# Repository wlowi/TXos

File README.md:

# TXos

Diese Software ist ein Beispiel für eine RC Sender firmware.<br/>
Es wird keine Haftung für Schäden jeglicher Art übernommen.

Bitte beachten Sie die Lizenz.

---

This is an example of a RC transmitter software.<br/>
In no event shall the authors or copyright holders be liable for any claim, damage or other liability.

Please obey the license.

---

[Bedienungsanleitung](MANUAL.md)

[Robbe Supra PCMS Umbau](SUPRA.md)

<span style="color:red">Achtung: Crossfire Protokoll ist neu und noch nicht vollständig getestet.</span>

[Crossfire / ELRS Howto](ELRS.md)

---

## Unterstützte Hardware

### Arduino CPU Board

- Joy-IT ADR MEGA2560PRO
- ESP32 DevKit (EXPERIMENTELL UND UNGETESTED, NICHT BENUTZEN!)

### Display

- ST7735 1,8" Color TFT Display

### Drück-Dreh Encoder

- Z.Bsp. von ALPS

### PPM HF-Module

- Z.Bsp. Spektrum Modul für Graupner MC-24 / MC-22 oder Jeti TU2 Modul.

### Seriell angesteuerte HF-Module

<span style="color:red">Achtung: EXPERIMENTELL UND UNGETESTED, NICHT BENUTZEN!</span>

- Spektrum X1TXN
- ELRS Full Duplex (interne Module) Bzw. Empfänger mit RxAsTx Firmware.

---

## Features

- Bis zu 6 Analoge Eingänge
- Bis zu 4 Eingänge für analogen Trimm
- Trimmspeicher
- Bin zu 6 Schalteingänge für 2 oder 3 Stufenschalter
- 12 Interne Kanäle
    MOT, QR, QR2, HR, SR, WK, WK2, LK, LK2, Fwk, K8, K9
    MOT = Motor
    QR = Querruder
    HR = Höhenruder
    SR = Seitenruder
    WK = Wölbklappen
    LK = Landeklappen
    Fwk = Fahrwerk
    K8, K9 = freie Kanäle
- Bis zu 12 Servo Ausgänge
- PPM Erzeugung (22.5 mSec. Frames)
- Unterstützt serielles Spektrum HF Modul (X1TXN)
- Unterstützt CRSF (Crossfire) Protokoll zur Ansteuerung von ELRS HF Modulen
- Spannungsüberwachung
- Display 8 x 13 Zeichen
- Deutsche und Englische Benutzeroberfläche
- Bedienung über Drück-Dreh Encoder
- Piepser
- Relais zum Ausschalten der HF-Modul Stromversorgung
- Relais zum Bedienen eines Bind-Tasters
- Geber Umkehr und Limitter
- Delta Mischer und V-Leitwerks Mischer
- Fertige Mischer für
    QR => SR
    QR => WK
    LK => QR
    LK => WK
    LK => HR
    WK => QR
    WK => HR
    HR => QR
    HR => WK
    SR => HR
- 3 Freie Mischer
- Kanal Laufzeit Verzögerung bis 10 Sek. (Ende zu Ende)
- 3 Geberschalter
- 3 Schaltkanäle
- 14 Modellspeicher
- 3 Flugphasen (aus Normal, Thermik, Speed, Start, Landung, Akro, Akro2, Strecke, Schlepp)
- Phasentrim für QR,WK,LK,HR
- Dual Rate und Exponential Funktion über Phasen für QR, SR und HR
- 3 Logische Schalter. (Boolsche Verknüpfung von bis zu 3 Schaltern)
- Freie Zuordnung der Geber zu Kanälen
- Freie Zuordnung der Kanäle zu Servo Ausgängen
- Servo Mitte, Umkehr und Limitter
- Timer (Wahlweise Gasabhängig)
- Motor-Aus Schalter
- Bind Funktion (Falls Support vom HF-Modul besteht)
- Reichweiten Test Funktion (Falls Support vom HF-Modul besteht)
- Servo Monitor
- Schalter Monitor
- Import und Export der Modelle zum PC über USB Schnittstelle

---

## Blockschaltbild der Funktionen

---

## Change History

```
0.5.19 Some UI improvements.
       Keep value of logical "Mot" channel to correct value if engine cut is enabled. 
0.5.18 CRSF and Spektrum Telemetry. First cut. 
0.5.17 Disable sleep. Fix input names array.
0.5.16 CRSF Protokol
0.5.15 Serielles Spektrum Protokol
0.5.14 internes Release
0.5.13 Notorstart Modul
0.5.12 Veränderte schaltung der Flugphasen
0.5.11 Logische Schalter: invertierte Schalter.
0.5.10 Timer wahlweise Gasabhängig.
       Alle Schalter in SWx umbenannt.
0.5.9 Landeklappen Modul.
0.5.8 Watchdog fix beim schreiben ins EEPROM und serial I/O
0.5.7 Servo Verzögerung Modul.
0.5.6 Servo Weg Modul.
0.5.5 Experimental ESP 32 support.
0.5.4 External user terminal support.
0.5.3 Experimental external user terminal support.
0.5.2 Template based configuration
0.5.1 Modul import fixed. Geber Weg getrennt pos. und neg.
0.5.0 Modell import/export. Modell management.
```

---

## Installation

### Übersetzen mit der Arduino IDE

#### Für ADR MEGA2560PRO

Benötigte Arduino Libraries
- Adafruit ST7736 and ST7789 Library
- Adafruit GFX Library

```
cd TXos
./mklinks atmega2560
```

Dieses Kommando verlinkt die Dateien im `src` Verzeichnis nach `TXos`.

Fall noch keine lokale Konfigurationsdtei TXosLocalConfig.h existiert wird diese von einer Musterdatei kopiert und muss an die eigen Hardware konfiguration angepasst werden.

Mit der Arduino IDE kann dann in diesem Verzeichnis TXos compiliert werden.

Notwendige Einstellungen der Arduino IDE

TO_BE_COMPLETED

#### Für ESP32 (EXPERIMENTELL UND UNGETESTED, NICHT BENUTZEN!)

Benötigte Arduino Libraries
- TFT_eSPI

```
cd TXos
./mklinks esp32
```

Mit der Arduino IDE kann dann in diesem Verzeichnis TXos compiliert werden.

Notwendinge Einstellungen der Arduino IDE

---

### Grundsätzliche Konfiguration:

Wechsel zu Verzeichnis TXos/TXos

Unter Linux ./mklinks.sh \<Platform\><br/>
ausführen.

Unter Windows mkcopy.bat \<Platform\><br/>
ausführen.

Als Platform wird zur Zeit nur atmega2560 unterstützt.

Existiert noch keine Datei TXosLocalConfig.h wird diese aus TXosLocalConfig.template neu erzeugt.

Konfiguration in TXosLocalConfig.h anpassen.

Hier werden eingestellt:

- Die Sprache der Benutzeroberfläche
- Das verwendete HF Modul
- Die Anzahl der PPM Kanäle
- Die Anzahl der Analog Kanäle
- Die Anzahl der Schalter (mechanische, logische und Sonderschalter)
- Die Anzahl der Flugphasen
- Die Anzahl der freien Mischer

Beispiel:

```

$ ./mklinks.sh atmega2560
Configuring for atmega2560
Link from ../src
   ../src/Comm.cpp  =>  Comm.cpp
   ../src/ConfigBlock.cpp  =>  ConfigBlock.cpp
   ../src/HomeScreen.cpp  =>  HomeScreen.cpp
  .
  .
  .
   atmega2560/OutputImpl.h  =>  OutputImpl.h
   atmega2560/PortsImpl.h  =>  PortsImpl.h

Local config does not exist.
A new TXosLocalConfig.h has been generated by copying the template file.
Please modify your local config to your needs.

```

---

## TXos Simulator

Der Simulator verwendet die `wxWidgets` library. Zum installieren:

```
apt install gcc make libwxgtk3.0-gtk3-dev

cd src
make clean
make -j
./TXosTest
```

---

## Unit test

```
cd test
make clean
make -j unittest
./TXosUnitTest
```

Achtung: `make clean unittest` funktioniert nicht!

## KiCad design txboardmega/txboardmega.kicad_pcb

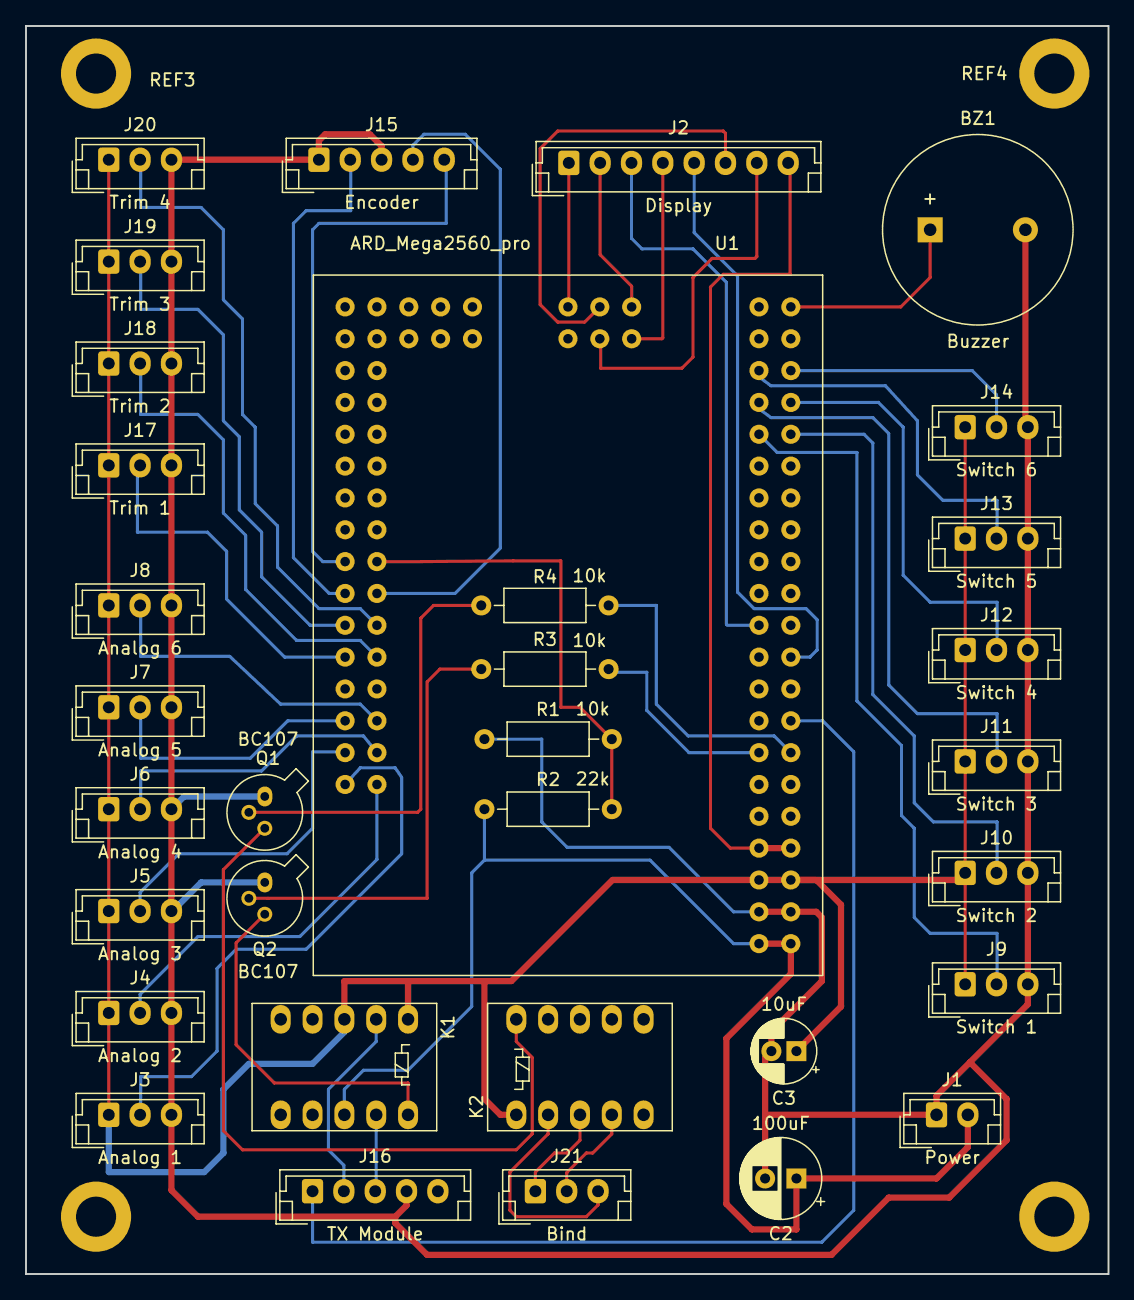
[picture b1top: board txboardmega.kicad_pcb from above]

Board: 2 copper layers, 86.4 x 99.6 mm, 37 parts (0 on the bottom side), 44 nets.

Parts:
BZ1: Buzzer; Buzzer_15x7.5RM7.6
C2: 100uF; CP_Radial_D6.3mm_P2.50mm
C3: 10uF; CP_Radial_D5.0mm_P2.00mm
J1: Power; JST_EH_B2B-EH-A_1x02_P2.50mm_Vertical
J2: Display; JST_EH_B8B-EH-A_1x08_P2.50mm_Vertical
J3: Analog 1; JST_EH_B3B-EH-A_1x03_P2.50mm_Vertical
J4: Analog 2; JST_EH_B3B-EH-A_1x03_P2.50mm_Vertical
J5: Analog 3; JST_EH_B3B-EH-A_1x03_P2.50mm_Vertical
J6: Analog 4; JST_EH_B3B-EH-A_1x03_P2.50mm_Vertical
J7: Analog 5; JST_EH_B3B-EH-A_1x03_P2.50mm_Vertical
J8: Analog 6; JST_EH_B3B-EH-A_1x03_P2.50mm_Vertical
J9: Switch 1; JST_EH_B3B-EH-A_1x03_P2.50mm_Vertical
J10: Switch 2; JST_EH_B3B-EH-A_1x03_P2.50mm_Vertical
J11: Switch 3; JST_EH_B3B-EH-A_1x03_P2.50mm_Vertical
J12: Switch 4; JST_EH_B3B-EH-A_1x03_P2.50mm_Vertical
J13: Switch 5; JST_EH_B3B-EH-A_1x03_P2.50mm_Vertical
J14: Switch 6; JST_EH_B3B-EH-A_1x03_P2.50mm_Vertical
J15: Encoder; JST_EH_B5B-EH-A_1x05_P2.50mm_Vertical
J16: TX Module; JST_EH_B5B-EH-A_1x05_P2.50mm_Vertical
J17: Trim 1; JST_EH_B3B-EH-A_1x03_P2.50mm_Vertical
J18: Trim 2; JST_EH_B3B-EH-A_1x03_P2.50mm_Vertical
J19: Trim 3; JST_EH_B3B-EH-A_1x03_P2.50mm_Vertical
J20: Trim 4; JST_EH_B3B-EH-A_1x03_P2.50mm_Vertical
J21: Bind; JST_EH_B3B-EH-A_1x03_P2.50mm_Vertical
K1: HF on; Relay_DPDT_FRT5
K2: Bind; Relay_DPDT_FRT5
Q1, Q2: BC107; TO-18-3
R1, R3, R4: 10k; R_Axial_DIN0207_L6.3mm_D2.5mm_P10.16mm_Horizontal
R2: 22k; R_Axial_DIN0207_L6.3mm_D2.5mm_P10.16mm_Horizontal
REF1, REF2, REF3, REF4: MountingHole_3.2mm_M3_DIN965_Pad
U1: ARD_Mega2560_pro

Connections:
unnamed: BZ1.1, U1.42
unnamed: BZ1.2, C2.2, C3.2, J1.1, J3.3, J4.3, J5.3, J6.3, J7.3, J8.3, J9.3, J10.3, J11.3, J12.3, J13.3, J14.3, J15.1, J15.3, J16.4, J17.3, J18.3, J19.3, J20.3, Q1.1, Q2.1, R1.1, U1.3, U1.4
unnamed: C2.1, J1.2, K1.8, R2.1, U1.1, U1.2
unnamed: C3.1, J3.1, J4.1, J5.1, J6.1, J7.1, J8.1, J9.1, J10.1, J11.1, J12.1, J13.1, J14.1, J17.1, J18.1, J19.1, J20.1, K1.1, K1.3, K2.1, U1.5, U1.6
unnamed: J2.1, U1.81
unnamed: J2.2, U1.85
unnamed: J2.3, U1.21
unnamed: J2.4, U1.86
unnamed: J2.5, U1.20
unnamed: J2.6, U1.83
unnamed: J2.7, U1.84
unnamed: J2.8, U1.7, U1.8
unnamed: J3.2, U1.43
unnamed: J4.2, U1.44
unnamed: J5.2, U1.45
unnamed: J6.2, U1.46
unnamed: J7.2, U1.47
unnamed: J8.2, U1.48
unnamed: J9.2, U1.33
unnamed: J10.2, U1.34
unnamed: J11.2, U1.35
unnamed: J12.2, U1.36
unnamed: J13.2, U1.37
unnamed: J14.2, U1.38
unnamed: J15.2, U1.55
unnamed: J15.4, U1.56
unnamed: J15.5, U1.57
unnamed: J16.1, U1.16
unnamed: J16.2, K1.2
unnamed: J16.3, K1.9
unnamed: J17.2, U1.51
unnamed: J18.2, U1.52
unnamed: J19.2, U1.53
unnamed: J20.2, U1.54
unnamed: J21.1, K2.3
unnamed: J21.2, K2.4
unnamed: J21.3, K2.2
unnamed: K1.10, Q2.3
unnamed: K2.10, Q1.3
unnamed: Q1.2, R4.2
unnamed: Q2.2, R3.1
unnamed: R1.2, R2.2, U1.58
unnamed: R3.2, U1.13
unnamed: R4.1, U1.14

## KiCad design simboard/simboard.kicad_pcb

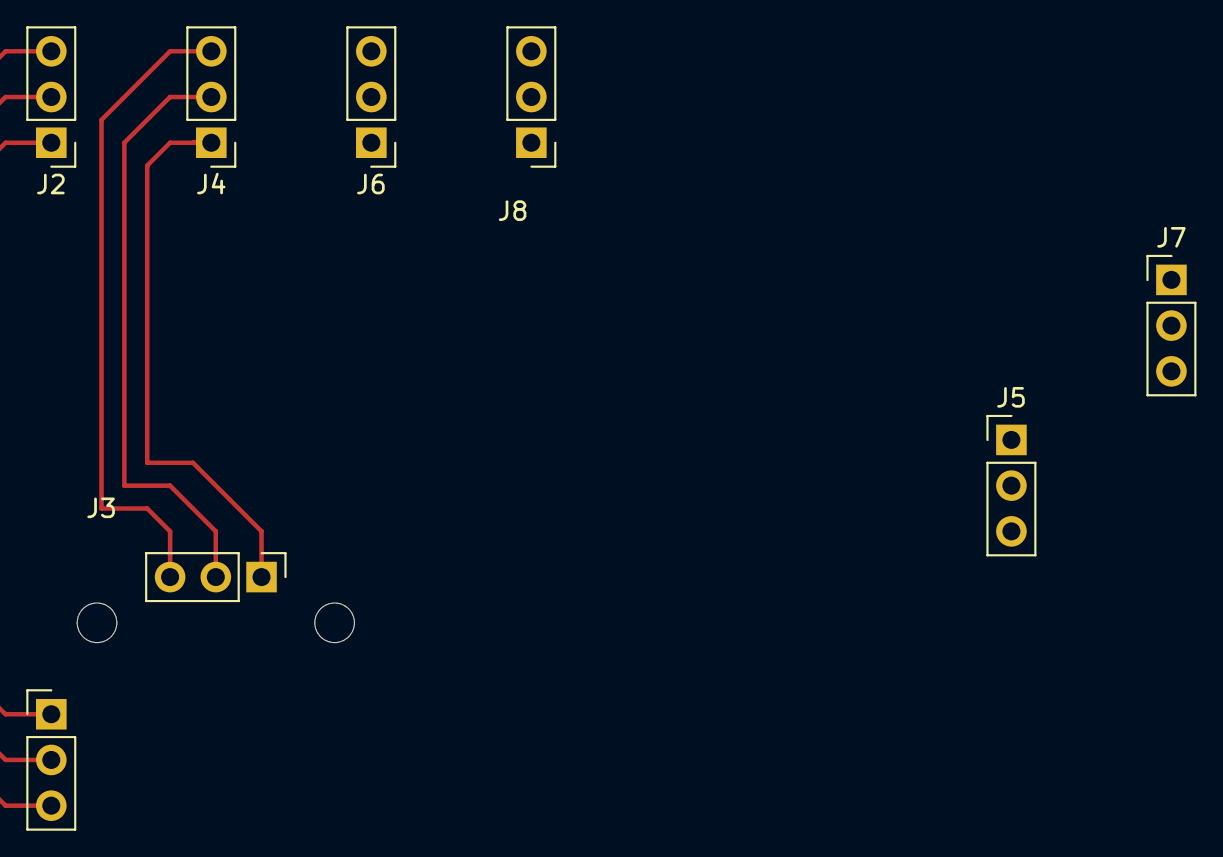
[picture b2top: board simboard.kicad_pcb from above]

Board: 2 copper layers, 8 parts (0 on the bottom side), 12 nets.

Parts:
J1, J2, J3, J4, J5, J6, J7, J8: Conn_01x03; PinHeader_1x03_P2.54mm_Vertical

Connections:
unnamed: J1.1, J2.1
unnamed: J1.2, J2.2
unnamed: J1.3, J2.3
unnamed: J3.1, J4.1
unnamed: J3.2, J4.2
unnamed: J3.3, J4.3
unnamed: J5.1, J6.1
unnamed: J5.2, J6.2
unnamed: J5.3, J6.3
unnamed: J7.1, J8.1
unnamed: J7.2, J8.2
unnamed: J7.3, J8.3

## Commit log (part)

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2022-04-13 Added src/default. Added gitignore
2022-04-30 Remote control simulation test framework.
2022-05-01 EEPROM emulation; ModuleManager; ServoReverse
2022-05-01 PPM improvements. KICAD Layout
2022-05-06 Intermediate checkin.
2022-05-18 SelectList added
2022-05-20 Table editable
2022-05-22 Some reorg
2022-05-23 Model edit module
2022-05-25 Fixed model select
2022-05-25 Fixed name editing
2022-05-25 Added EngineCut module
2022-05-31 Implementation or atmega2560
2022-05-31 Add Kicad design for mega 2560
2022-06-16 PPM generation implemented.
2022-06-19 PCB update
2022-06-30 txmegaboard updates and code cleanup
2022-06-30 Fixed LOG parameters
2022-07-03 Switch states and some cleanup
2022-08-21 Add ServoMonitor and SwitchMonitor
2022-08-27 Controls refactored
2022-09-10 Board for Robbe Supra
2022-09-25 Added Ports and Buzzer
2022-09-29 Complete Ports and Buzzer
2022-11-19 UI improvements. System setup (incomplete).
2022-11-24 SystemSetup module added.
2022-11-25 UI improvements part 2
2022-11-25 UI improvements part 3
2022-11-26 CalibrateSticks added
2022-11-26 UI minor fixes
2022-11-26 SystemConfig save and load
2022-11-27 CalibrateTrim added. V0.1.4
2022-11-27 CLEAR Button, UI: Correct go-back handling.
2022-11-27 Bind and RangeTest added. V0.1.5
2022-11-30 Encoder fix. Query switches. V0.1.6
2022-11-30 Improved string edit
2022-12-01 Cell switch edit. V0.1.7
2022-12-02 VccMonitor added.
2022-12-02 VccMonitor complete. Display messages added. V0.1.8
2022-12-03 Phases added. V0.1.9
2022-12-04 DualExpo fixes. V0.1.10
2022-12-06 Permanent alarm sound. Dual rate fixes.
2022-12-06 Buzzer fix
2022-12-06 Timer module config. Minor Cell changes.
2022-12-07 PhasesTrim and SwitchedChannels. Vcc monitor fix. V0.1.11
2022-12-08 AssignInput and ServoRemap
2022-12-08 DE support. DualExpo fix. V0.1.13
2022-12-09 AnalogSwitch added.
2022-12-09 ChannelRange added. V0.1.14
2022-12-10 New switch data types and switch state editing.
2022-12-11 Statistics added. Timer working. V0.1.15
2022-12-11 PhaseTrim WK channel added.
2022-12-11 EngineCust status display. Statistics data type fix.
2022-12-13 Expo added. Channels renamed.
2022-12-13 Dual Rate fix.
2022-12-13 PhasesTrim added.
2022-12-14 Various fixes. 3 channel switches. Switches renamed. V0.1.17
2022-12-14 Model mixer UI.
2022-12-15 Fix crash in Cell switch edit. Bind/Rangetest screen update fix. Mix offset. V0.1.18
2022-12-15 ChannelReverse added. Ail>Flp mix fix. V0.1.19
2022-12-15 All Model mixer fixed, including aileror diff. V0.1.20
2022-12-16 General mixer. V0.1.21
2022-12-16 ChannelDelay added. V0.2.0
2022-12-17 UI improvements. V0.2.1
2022-12-19 Serial enabled./rmlinks.sh ChannelDelay fixed. Save SystemConfig after model load. V0.2.2
2022-12-20 Fix AIL>FLP Mixer. Add PPM statistics. V0.2.3
2022-12-21 UI improvements. V0.2.4
2022-12-22 Watchdog enabled. CPU sleep. Additional Statistics. UI improvements. V0.2.5
2022-12-23 LogicSwitch added. Fix switch state in Cell. V0.2.6
2022-12-24 Unittests first cut.
2022-12-26 Fix VTail and Delta mix. V0.2.7
2022-12-26 Minor fix to rotaty encoder.
2022-12-27 Refactor ConfigBlock and AssignInput. V0.2.8
2022-12-28 Unittests CalibrateSticks, CalibrateTrim
2022-12-29 Unittest: SwitchedChannels and AnalogSwitch
2022-12-29 Unittest ChannelRange and ChannelReverse
2022-12-30 Unittest AssignInput and ChannelDelay
2022-12-31 Some refactoring. V0.2.9
2023-01-02 New config block sizes. V0.2.10
2023-01-04 ModeAssign implemented. Mix mapping table removed. V0.2.11
2023-01-06 AnalogTrim implemented. Minor fixes. V0.2.12
2023-01-07 AssignInput to nothing. SwitchChannels always assigned to In7 - In9. Layout improvements. V0.2.13
2023-01-10 Directories renamed.
2023-01-10 PPM Timing change. Directory rename again...
2023-01-12 Copyright messages
2023-01-14 MANUAL.md: System menu documented. Switches renamed.
2023-03-28 PPM Timing fix. License change to MIT License. V0.3.1
2023-04-03 Changes in MANUAL.md
2023-04-06 Switch to TextUI. Temporary commit.
2023-04-07 Switch to TextUI. Temporary commit 2.
2023-04-07 Switch to TextUI complete. V0.4.0
2023-04-19 TextUI updated. PPM generator fixes. V0.4.1
2023-04-20 ServoTest modules added. V0.4.2
2023-04-23 Documentation and cleanup.
2023-07-02 Unittests fixed
2023-08-12 Model and system config export
2023-08-14 Fix ServoTest Module; Version 0.4.4
2023-10-28 Module rename Exporter to Comm
2023-10-28 KiCAD new file format
2024-01-04 Change frame time to 21msec. Don't move throttle channel in server test. V0.4.5
2024-01-07 Frame cycle time in usec.
2024-01-20 temp checkin
2024-01-27 Import Export Dictionary. V0.4.6
2024-02-09 Added SerialConsole
2024-02-18 Import temp checkin.
2024-02-20 Model import completed. Model management (remove/copy). V0.5.0
2024-02-26 Model import fixed. Added sep. ChannelRange for neg and pos. Modules reordered. V0.5.1
2024-03-01 Cleanup.
2024-03-01 PCB schema pdf and layout images.
2024-03-04 Documentation
2024-03-09 Better template based configuration. V0.5.2
2024-03-23 Experimental external user terminal support. V0.5.3
2024-04-01 Added ReliableStream class from TextUI. User terminal support completed. V0.5.4
2024-04-01 Fix test.
2024-05-09 User Manual updated to 0.5.4
2024-05-10 ESP32 port. Temporary checkin.
2024-05-10 Fixed Vcc update in VccMonitor.
2024-05-11 PPM generation on ESP32
2024-05-12 ADC read on ESP32
2024-05-20 Buzzer on ESP32. FIx PPM generation.
2024-05-20 Doc update for ESP32.
2024-06-16 Robbe Supra conversion doc
2024-07-14 Windows mkcopy rmcopy batch files.
2025-08-16 ServoRange module added. V0.5.6
2025-08-16 ServoDelay module added. V0.5.7
2025-08-17 Fix watchdog hit while EEPROM write and serial I/O. V0.5.8
2025-08-20 AirBrakes module. V0.5.9
2025-08-21 Documentation updated
2025-09-09 Thr. dependent timer. Switches renamed to SWx. V0.5.10
2025-09-10 LogicSwitch: Support inverted switches. V0.5.11
2025-09-16 Reworked flight phase switching. V0.5.12
2025-09-20 ESP32 fixes.
2025-09-26 Add MotorStart module. V0.5.13
2025-09-28 Move bind and range test to OutputImpl
2026-02-03 Serial Output for Spektrum HF Module. V0.5.15
2026-02-06 Crossfire Serial Output Support. V0.5.16
2026-02-08 Disable sleep. Trim and Stick ADC reverse. Fix input name array. V0.5.17
2026-02-15 Telemetry first cut.
2026-02-24 Doc. updated. Minor changes. V0.5.18
